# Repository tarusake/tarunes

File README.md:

# tarunes

tarunes is a NES-compatible hardware design written in Veryl. It includes a 6502-family CPU, NES-style PPU / APU, CPU and PPU buses, memory blocks, an HDMI 480p scaler, I2S audio output, and SFC controller input.

The design supports Verilator + SDL2 simulation and Tang Nano 20K hardware. It converts an iNES ROM into PRG / CHR HEX files and displays either the internal 256x240 video output or the 720x480 HDMI output.

No commercial ROM files are included in this repository.

## Project Layout

```text
tarunes/
├── Veryl.toml          # Veryl project configuration
├── Makefile            # Build, ROM conversion, and simulation targets
├── nes2hex.py          # Convert an iNES ROM into PRG / CHR HEX files
├── csv_to_opcodenotrace.py
│                       # Extract PC/opcode rows from a Gowin CSV trace
├── collapse_cpu_trace_loops.py
│                       # Collapse long wait loops in CPU traces
├── src/
│   ├── top.veryl       # Top-level module
│   ├── cpu.veryl       # CPU core
│   ├── cpu_pkg.veryl   # CPU instruction and decode definitions
│   ├── ppu.veryl       # Picture Processing Unit (PPU)
│   ├── ppu_pkg.veryl   # PPU register, OAM, and address definitions
│   ├── nes_pkg.veryl   # Shared NES address map and timing constants
│   ├── apu.veryl       # Audio Processing Unit (APU)
│   ├── i2s.veryl       # I2S transmitter
│   ├── hdmi_480p_scaler.veryl
│   │                   # Convert 256x240 video to 720x480 HDMI timing
│   ├── sfc_controller.veryl
│   │                   # SFC controller polling
│   ├── controller.veryl # $4016/$4017 controller registers
│   ├── oam_dma.veryl   # $4014 OAM DMA
│   ├── bus_cpu.veryl   # CPU bus decoder
│   ├── bus_ppu.veryl   # PPU bus decoder
│   ├── bus_if.veryl    # Bus interface
│   ├── memory.veryl    # Memory module
│   ├── tb_top.sv       # SystemVerilog testbench
│   └── tb_top.cpp      # C++ Verilator testbench driver
├── target/             # RTL generated by Veryl
├── tarunes_TangNano20k/
│                       # Tang Nano 20K wrapper, constraints, and Tcl build
├── tarunes_TangPrimer20k/
│                       # Tang Primer 20K Dock wrapper, constraints, and Tcl build
└── obj_dir/            # Verilator build output
```

## Requirements

Ubuntu 24.04 LTS or later is recommended for the simulation environment.

- [Verilator](https://www.veripool.org/verilator/) 5.0 or later
- [Veryl](https://github.com/veryl-lang/veryl) 0.22.1
- SDL2 development package (`sdl2-config`)
- SDL2_image development package (`SDL2_image.pc` visible to `pkg-config`)
- GNU Make
- GCC or Clang with C++17 support

Example for Ubuntu / Debian:

```bash
sudo apt install verilator libsdl2-dev libsdl2-image-dev make g++
```

### Installing Veryl

Veryl can be installed with `verylup`, the official Veryl toolchain installer. This project currently uses Veryl `0.22.1`.

Using Cargo:

```bash
cargo install verylup
verylup setup
verylup install 0.22.1
verylup default 0.22.1
veryl --version
```

`verylup setup` is only needed for the first installation. If `veryl --version` reports `veryl 0.22.1`, the toolchain is ready.

To update the installed toolchain:

```bash
verylup update
```

You can also install `verylup` by downloading a binary from its release page and placing it somewhere in your `PATH`. See [verylup: Veryl toolchain installer](https://veryl-lang.org/blog/verylup-veryl-toolchain-installer/) for details.

## Build

Place `<ROM name>.nes` at the repository root and run `make`.
By default, the build expects `helloworld.nes` and generates `helloworld_prg.hex` and `helloworld_chr.hex`.

```bash
make
```

To use another ROM, pass its basename through `ROM`:

```bash
make ROM=sample
```

This converts `sample.nes` into `sample_prg.hex` and `sample_chr.hex`, then passes them to Verilator through the `PROM_PATH` and `CROM_PATH` parameters.

To build with the APU disabled:

```bash
make ENABLE_APU=0
```

### Tang Nano 20K

Install Gowin EDA and make sure `gw_sh` is available in `PATH`. Then build the
bitstream with:

```bash
make tangnano20k ROM=sample
```

The bitstream is generated at
`tarunes_TangNano20k/impl/pnr/tarunes_tangnano20k.fs`. The board implementation
uses a Veryl TMDS encoder with Gowin `CLKDIV`, `OSER10`, and `TLVDS_OBUF`
primitives, so the encrypted Gowin DVI TX IP is not required.

APU audio is output through the board I2S pins. See
[`tarunes_TangNano20k/README.md`](tarunes_TangNano20k/README.md) for board pins,
clocking, and other details.

### Tang Primer 20K Dock

Tang Primer 20K uses the same Veryl TMDS encoder and has its own device and pin
constraints:

```bash
make tangprimer20k ROM=sample
```

The bitstream is generated at
`tarunes_TangPrimer20k/impl/pnr/tarunes_tangprimer20k.fs`. See
[`tarunes_TangPrimer20k/README.md`](tarunes_TangPrimer20k/README.md) for reset,
clock, audio, and Dock details.

## Simulation

Build and run the simulator:

```bash
make run
```

The simulator opens an SDL2 window and displays the internal 256x240 video output at 2x scale. A normal run also prints a CPU trace and writes `wave.fst`, which can be inspected with tools such as GTKWave.

For a faster run without the CPU trace or waveform output:

```bash
make run-fast
```

`run-fast` also uses an optimized simulator built without waveform tracing support.

Play APU audio in real time through SDL:

```bash
make run-fast ARGS="--audio"
```

Run another ROM:

```bash
make run ROM=sample
```

Generate a CPU execution trace for [Konata](https://github.com/shioyadan/Konata):

```bash
make run-fast ARGS="--konata tarunes.log --frames 1"
```

Open `tarunes.log` in Konata to inspect each instruction's internal CPU state transitions. The log also includes the PC, disassembly, instruction bytes, register values, frame number, and CPU cycle.

Stop after a fixed number of frames:

```bash
make run ARGS="--fast --frames 10"
```

Capture the HDMI 480p output instead of the internal 256x240 output:

```bash
make run-fast ARGS="--capture-hdmi --frames 10"
```

Runtime options:

- `--fast`: Disable CPU trace and waveform output
- `--audio`: Play APU audio through the SDL audio device
- `--capture-hdmi`: Display and save the 720x480 HDMI output
- `--frames N`: Stop after N completed frames
- `--dump-audio PATH`: Set the WAV output path
- `--dump-vram PATH`: Dump VRAM when the simulator exits
- `--log-ppu-writes PATH`: Log `$2006` / `$2007` writes
- `--konata PATH`: Write a Kanata v4 CPU execution trace
- `--dump-state`: Print a small PPU / WRAM state dump on exit

On exit, the simulator writes the last video frame to `last_frame.png` and audio to `apu.wav`.

Clean generated files:

```bash
make clean
```

## ROM Conversion

NES ROM files (`.nes`) can be converted into HEX files for simulation memory:

```bash
./nes2hex.py <input.nes>
```

Example:

```bash
./nes2hex.py helloworld.nes
```

Outputs:

- `helloworld_prg.hex`: PRG ROM for the CPU side
- `helloworld_chr.hex`: CHR ROM for the PPU side

For CHR RAM cartridges, no `*_chr.hex` file is generated because the ROM does not contain CHR ROM data.

## PPU

`src/ppu.veryl` provides:

- Background rendering
- Basic scroll register behavior (`v` / `t` / `w` / fine X)
- 8x8 sprite rendering through `$2003` / `$2004` OAM access
- `$4014` OAM DMA from WRAM to OAM
- VRAM / CHR ROM access control
- Palette RAM and NES palette based RGB output
- Video timing generation
- NMI / vblank / sprite zero hit

CPU-side VRAM and Palette RAM access is done through `$2006` / `$2007` style registers. Sprites are written into internal OAM through `$2003` / `$2004` style registers, then combined with background pixels in the PPU rendering path. The rendering path reads CHR ROM and VRAM, then the top-level module produces both the internal palette index and HDMI RGB output.

The current sprite implementation supports 8x8 mode, transparent pixels, sprite palettes, horizontal and vertical flipping, background priority, and sprite zero hit. `$4014` OAM DMA supports WRAM (`$0000-$1FFF`) as the transfer source, but the exact 513/514-cycle timing difference is not implemented. 8x16 sprites and sprite overflow are not implemented yet.

## CPU

`src/cpu.veryl` implements the main official 6502-family opcodes needed by the current design:

- Load / store: `LDA`, `LDX`, `LDY`, `STA`, `STX`, `STY`
- Arithmetic / logic: `ADC`, `SBC`, `CMP`, `CPX`, `CPY`, `AND`, `ORA`, `EOR`, `BIT`
- Shift / rotate / increment: `ASL`, `LSR`, `ROL`, `ROR`, `INC`, `DEC`, `INX`, `INY`, `DEX`, `DEY`
- Branch / jump / subroutine: `BCC`, `BCS`, `BNE`, `BEQ`, `BPL`, `BMI`, `BVC`, `BVS`, `JMP`, `JSR`, `RTS`, `RTI`, `BRK`
- Stack / transfer / flags: `PHA`, `PLA`, `PHP`, `PLP`, `TAX`, `TXA`, `TAY`, `TYA`, `TSX`, `TXS`, `SEI`, `SEC`, `CLI`, `CLD`, `CLC`, `SED`, `CLV`, `NOP`

Unimplemented opcodes are treated as `INVALID`. Unofficial opcodes are currently out of scope.

## APU / Audio

`src/apu.veryl` implements the basic registers and counters for two pulse channels, triangle, and noise. DMC is not implemented.

- `$4000-$4007`: pulse 1 / pulse 2
- `$4008-$400B`: triangle
- `$400C-$400F`: noise
- `$4015`: channel enable / status
- `$4017`: frame counter

The APU produces 8-bit samples. The top-level module stores them in a small FIFO, and `src/i2s.veryl` outputs them as I2S. The Verilator testbench can also save them as a WAV file.

## Video Output

`src/hdmi_480p_scaler.veryl` converts the 256x240 PPU output into a 720x480 HDMI 480p timing stream. In the Verilator testbench, `--capture-hdmi` captures frames from the HDMI-side RGB / sync / data-enable outputs.

## Memory Map

CPU side:

- `$0000-$1FFF`: WRAM
- `$2000-$2007`: PPU registers (`$2003`: OAMADDR, `$2004`: OAMDATA)
- `$4000-$4017`: APU / OAM DMA / controller registers
- `$4014`: OAM DMA, as part of `$4000-$4017`
- `$4016-$4017`: controllers
- `$8000-$FFFF`: PRG ROM

PPU side:

- `$0000-$1FFF`: CHR ROM
- `$2000-$3EFF`: VRAM
- `$3F00-$3F1F`: Palette RAM

## References

The NES-compatible behavior in this project is based mainly on the following public specification resources:

- [NESdev Wiki](https://www.nesdev.org/wiki/Nesdev_Wiki)
- [Emulator tests](https://www.nesdev.org/wiki/Emulator_tests)
- [CPU unofficial opcodes](https://www.nesdev.org/wiki/CPU_unofficial_opcodes)
- [PPU scrolling](https://www.nesdev.org/wiki/PPU_scrolling)
- [PPU palettes](https://www.nesdev.org/wiki/PPU_palettes)
- [APU](https://www.nesdev.org/wiki/APU)
- [APU Mixer](https://www.nesdev.org/wiki/APU_Mixer)
- [APU Length Counter](https://www.nesdev.org/wiki/APU_Length_Counter)
- [NES研究室 - サンプル](https://tekepen.com/nes/sample.html)

## Japanese README

Japanese documentation is available in [README_jp.md](README_jp.md).

## License

This project is released under the MIT License.

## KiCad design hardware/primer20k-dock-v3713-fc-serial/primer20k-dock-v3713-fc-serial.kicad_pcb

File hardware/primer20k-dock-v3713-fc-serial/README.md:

# Tang Primer 20K Dock V3713 - FC NROM serial cartridge reader

Tang Primer 20K Dock V3713を残したまま、実ファミコンカートリッジの
PRG ROM/CHR ROMを起動時に読み出すためのDock直挿しアダプタ基板。

## 対応範囲

- 日本版FC 60ピンカートリッジ
- Mapper 0（NROM-256、PRG ROM 32 KiB＋CHR ROM 8 KiB）
- Dock PMOD0への1コネクタ直挿し（ケーブル不要）
- PMOD1/2/3位置を一続きに切り欠き、別PMODをDockへ直接挿せる
- Dockの3.3 Vから基板上で5.0 Vを生成
- カートリッジ電源をFPGAからON/OFF
- 電源OFF時はレベル変換ICから全74HC595出力をHi-Z化し、逆給電を防止

本基板はNROMカートリッジのPRG/CHR ROMを起動時に読み出す。ダンプ後に
カートリッジ電源を切り、tarunes本体は取得済みイメージから動作する。
カートリッジバスのリアルタイムパススルーやMMC書込み回路は実装しない。

## Dock接続

DockのPMOD0へ直接挿す。HDMI、Ethernet、
USBデバッガ、オーディオ出力には干渉しない。

`ciniml/TangFPGAExtensions` の `TangPrimer_PmodExtender.kicad_pcb`を基準にする。
Dock側4コネクタは同一Yで隣接間隔19.10 mm。J2をPMOD0へ挿し、
PMOD1/2/3位置をまとめて露出する幅47.5 mm、深さ15 mmの切り欠きを設ける。
J2は秋月 `PH-2x40SG(6.1/6.1)`（販売コード112180）から2x6を1個切り出し、
基板下向きに手実装する。6.1 mmの嵌合長を確保し、JLCPCBの実装対象からは除外する。
JLCPCBで波はんだ実装まで依頼する場合の代替は
`PZ254-2-06-Z-8.5`（C2894967、嵌合長6 mm）だが、本リリースBOMでは採用しない。

PMOD3には既存のPMOD-SFCを切り欠きからDockへ直接挿せる。tarunesの既存配置は
`sfc_data=N8`、`sfc_clk=N7`、`sfc_latch=B11`で、いずれもJ5に出ている。
J5はRGB LCD端子と信号を共有するため、PMOD-SFC使用中はRGB LCDを接続しない。
HDMI出力とは競合しない。

PMOD-SFCパススルー回路は実装しない。PMOD-SFCへの電源と信号はすべて
Dock PMOD3から直接供給される。

PMOD1/2/3には本基板から電源も信号も接続しない。

| FPGA ball | Adapter signal | Direction |
|---|---|---|
| P9 | CART_SCLK | Dock -> adapter |
| T9 | CART_MOSI | Dock -> adapter |
| T8 | CART_RCLK | Dock -> adapter |
| P8 | CART_PL_N | Dock -> adapter |
| R8 | CART_MISO | adapter -> Dock |
| T6 | CART_PWR_EN | Dock -> adapter |
| P6, T7 | NC | - |

J14 pin 6/T9はDock上のWS2812にも接続されているため、ROM読み出し中にLEDが
点滅する。電気的競合はない。GowinプロジェクトではT9に
`set_option -use_sspi_as_gpio 1`が必要。

## シリアルプロトコル

秋月TC74HC595AFを5個（40 bit出力）、TC74HC165APを2個（16 bit入力）として
使用し、すべて5 Vで動作する。Dockの3.3 V制御信号はTC74VHCT540AFで
5 Vへ変換する。540は反転型なので、FPGAはMOSI/SCLK/RCLK/PLを反転して
出力する。MISOは1 kΩ/2 kΩの抵抗分圧で3.3 Vへ変換する。

出力チェーンは最初に送ったbitがU5側へ移動する。`shift-map.csv`を正本とする。

1. `CART_PWR_EN=0`で開始する。U9が595出力をHi-Zに保つ。
2. `CART_PWR_EN=1`後5 ms待つ。
3. 40 bitをMSB firstで送信し、`CART_RCLK`をLow→High→Lowにする。
4. 500 ns待ち、`CART_PL_N`をLowにして入力をラッチする。
5. `CART_PL_N=High`後、16 bitを読み出す。CPU D0-D7に続いてPPU D0-D7。
6. 全ROM読出し後`CART_PWR_EN=0`。U9が595出力をHi-Zに戻す。

PMODからU9までの4本は反転前の信号で、U9出力が実際の595/165制御信号に
なる。上記手順はカートリッジ側で観測する論理極性を示す。

初版はNROM-256固定で、PRG 32 KiBとCHR 8 KiBを読み出す。MMC1/MMC3/MMC5、
CHR RAM、NROM-128の自動判別は対象外。

シリアルクロック上限は10 MHzとする。カートリッジアクセス待ちは500 ns以上。

## 電源条件

- Dock PMOD +3V3入力: 約400 mAまでを想定し、0.8 mm配線
- FC +5V出力: 200 mA連続を設計上限
- 秋月AE-XCL102D503CR-G（販売コード113065）: 5 V、最大210 mA
- TCK107AFロードスイッチ（販売コード116072）: FPGA正論理制御
- 電源投入中のカートリッジ抜き差し禁止
- Dockへ5 Vを逆給電しない

## 製造ファイル

PCBAは使用せず、JLCPCBへは`manufacturing/gerbers.zip`だけを投入する。
部品は`manual-parts.csv`に従って秋月から購入し、すべて手実装する。

- `gerbers.zip`
- `manual-parts.csv`
- `erc.rpt`, `drc.rpt`

`bom.csv`と`cpl.csv`はPCBA非使用を明示するためヘッダーのみで、アップロード
しない。

FCコネクタJ1はユーザー支給・DNP。調達品はAliExpress item
`1005007638566482`の選択肢E「For Famicom FC 60pin」（固定耳付き）。
信号端子部はFC規格とHirose `CR22A-60D-2.54DS(70)`の公式図面を
交差チェックし、以下でフットプリントを確定する。

- 信号ピン: 2x30、2.54 mmピッチ
- 列間: 5.08 mm
- 端子列の長さ: 29 x 2.54 = 73.66 mm
- 基板穴: 1.0 mm drill、1.8 mm pad（Hirose推奨の0.8 +0.2/-0 mmを包含）

AliExpress品の固定耳は寸法図がない。商品画像を2.54 mmピッチで
画像校正した参考値は、本体幅約87 mm、全長約124 mm、固定穴中心間
約115 mm。ただし写真透視の推定なのでPCB穴には使用ず、耳は基板の外へ
オーバーハングさせる。60本のはんだ端子で固定し、耳の固定穴は本設計では
使用しない。これにより、耳の実測待ちにせずGerberを確定できる。

## 再生成

KiCad 10とpcbnew Python moduleが必要。

```bash
./build.sh
```

## 発注設定

- 2層、FR-4、1.6 mm、1 oz（両面GNDポリゴン）
- HASL lead-freeまたはENIG
- 最小配線/間隔 0.20/0.15 mm（通常配線間隔0.20 mm、U9パッド間のみ0.16 mm）
- 銅箔－基板外形クリアランス 0.30 mm
- 最大外形 約85 x 55.12 mm（PMOD1/2/3に47.5 x 10.5 mmの連続切り欠き）
- Dock直挿し保持のため、単独ケース用M3取付穴は省略
- J1は実装しない

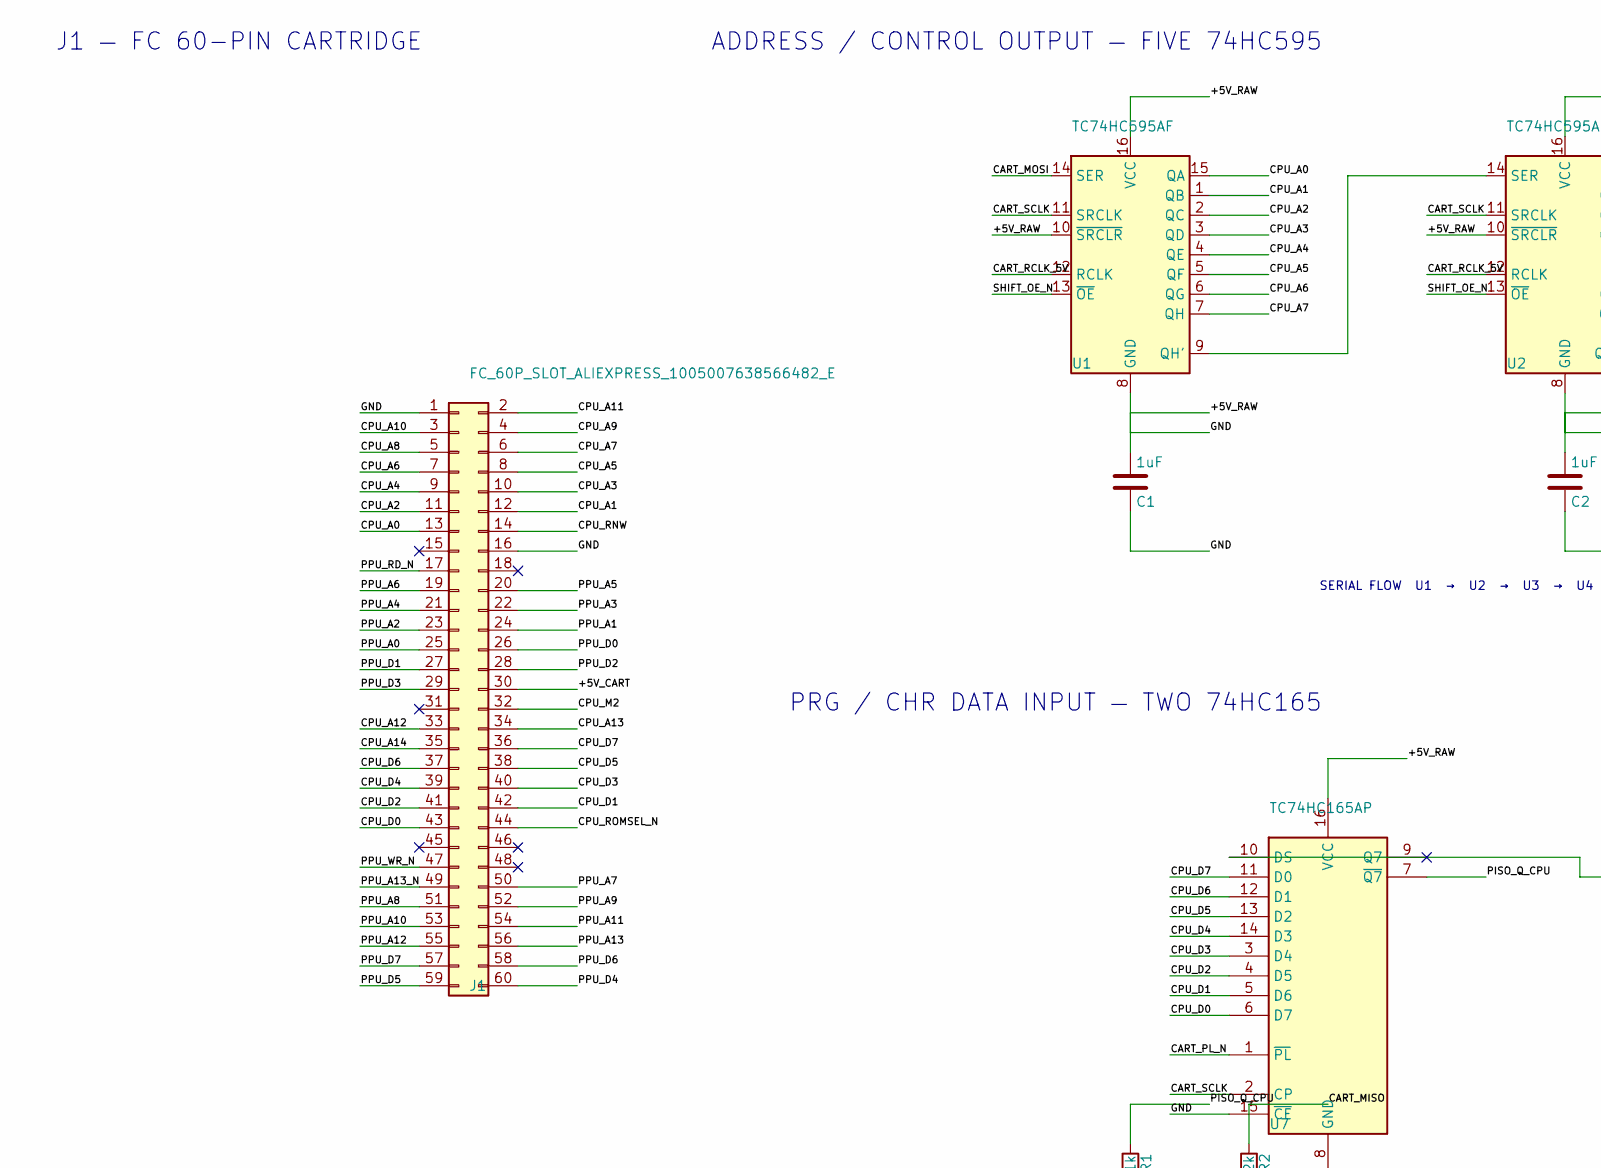
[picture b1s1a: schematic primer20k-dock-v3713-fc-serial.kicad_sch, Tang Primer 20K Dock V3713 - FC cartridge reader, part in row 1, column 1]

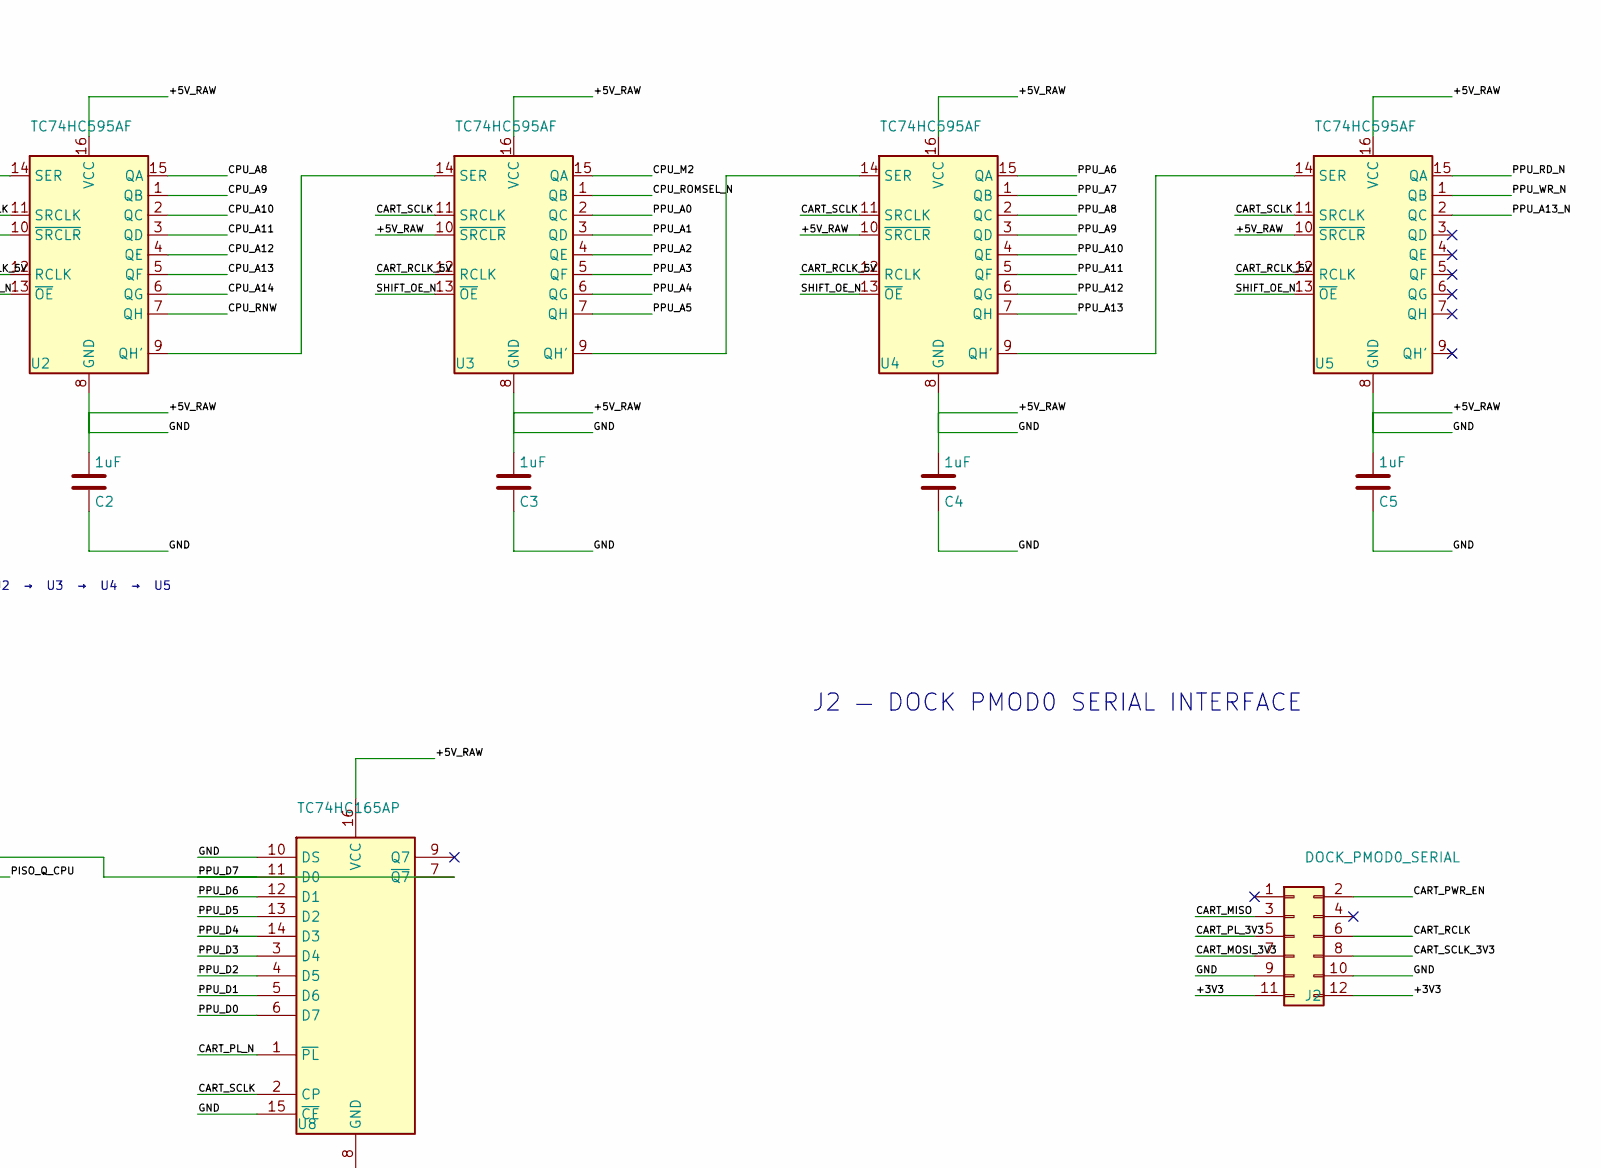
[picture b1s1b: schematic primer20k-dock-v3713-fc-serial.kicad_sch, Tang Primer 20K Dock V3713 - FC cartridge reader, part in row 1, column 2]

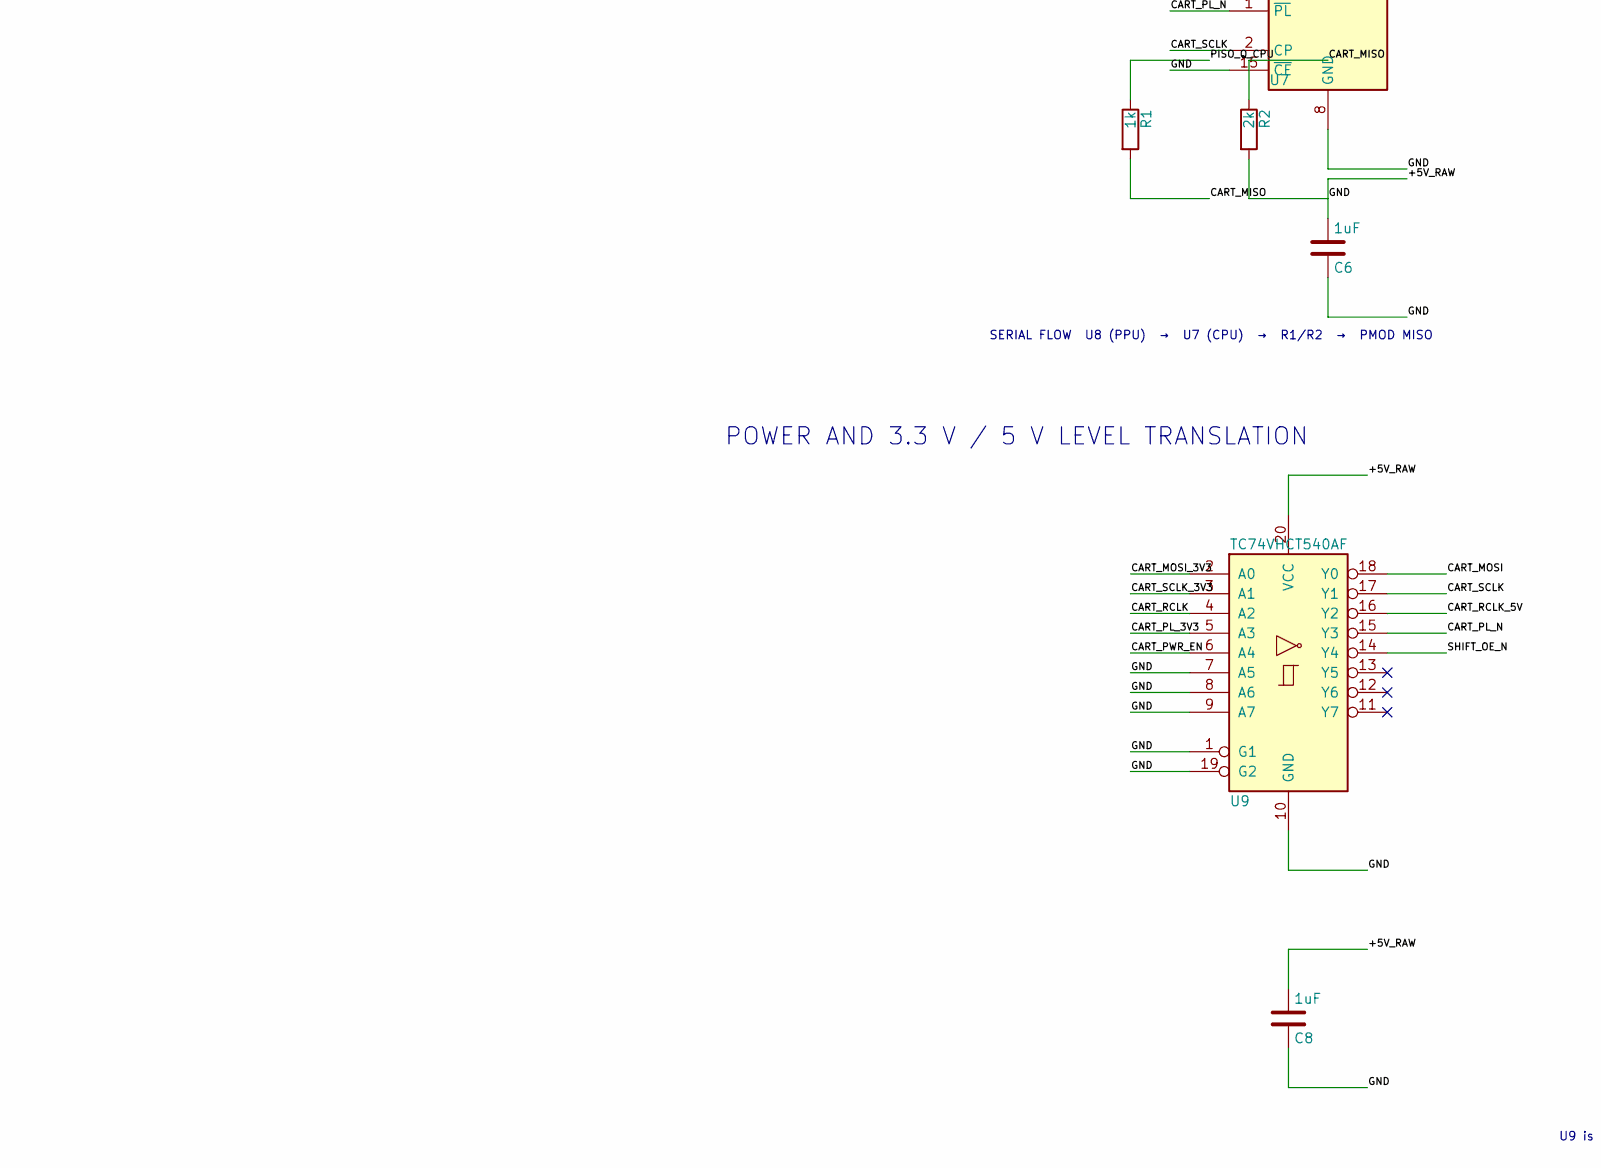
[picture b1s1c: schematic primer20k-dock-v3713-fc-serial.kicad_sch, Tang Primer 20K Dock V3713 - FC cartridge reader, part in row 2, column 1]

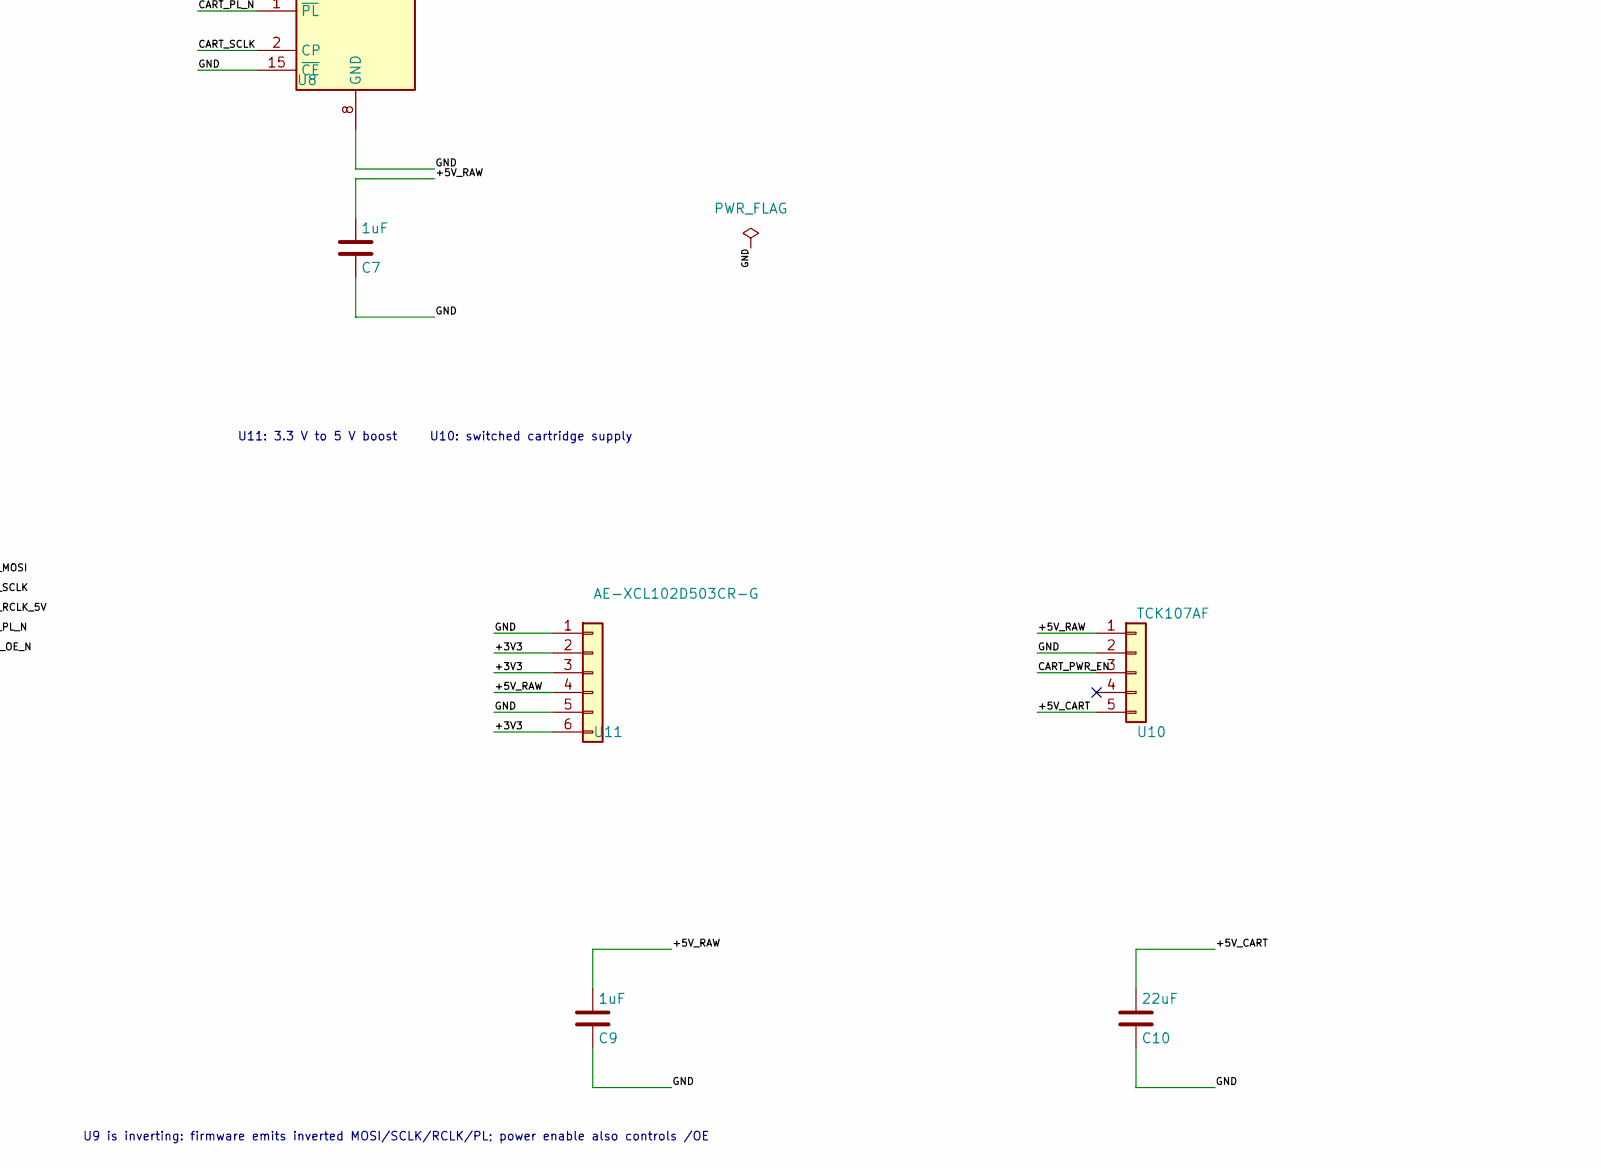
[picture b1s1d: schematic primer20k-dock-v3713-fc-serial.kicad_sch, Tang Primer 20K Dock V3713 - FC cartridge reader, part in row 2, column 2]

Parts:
C1, C2, C3, C4, C5, C6, C7, C8, C9: 1uF; C_0805_2012Metric
C10: 22uF; C_0805_2012Metric
J1: FC_60P_SLOT_ALIEXPRESS_1005007638566482_E; PinHeader_2x30_P2.54mm_Vertical
J2: DOCK_PMOD0_SERIAL; PinHeader_2x06_P2.54mm_Vertical
R1: 1k; R_Axial_DIN0207_L6.3mm_D2.5mm_P7.62mm_Horizontal
R2: 2k; R_Axial_DIN0207_L6.3mm_D2.5mm_P7.62mm_Horizontal
U1, U2, U3, U4, U5: TC74HC595AF; SOIC-16_3.9x9.9mm_P1.27mm
U7, U8: TC74HC165AP; DIP-16_W7.62mm
U9: TC74VHCT540AF; SOIC-20W_7.5x12.8mm_P1.27mm
U10: TCK107AF; SOT-23-5
U11: AE-XCL102D503CR-G; DIP-6_W7.62mm

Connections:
+3V3: J2.11, J2.12, U11.2, U11.3, U11.6
+5V_CART: C10.1, J1.30, U10.5
CART_MISO: J2.3, R1.2, R2.1
CART_MOSI: U1.14 (SER), U9.18 (Y0)
CART_MOSI_3V3: J2.7, U9.2 (A0)
CART_PL_3V3: J2.5, U9.5 (A3)
CART_PL_N: U7.1 (~PL), U8.1 (~PL), U9.15 (Y3)
CART_PWR_EN: J2.2, U9.6 (A4), U10.3
CART_RCLK: J2.6, U9.4 (A2)
CART_RCLK_5V: U1.12 (RCLK), U2.12 (RCLK), U3.12 (RCLK), U4.12 (RCLK), U5.12 (RCLK), U9.16 (Y2)
CART_SCLK: U1.11 (SRCLK), U2.11 (SRCLK), U3.11 (SRCLK), U4.11 (SRCLK), U5.11 (SRCLK), U7.2 (CP), U8.2 (CP), U9.17 (Y1)
CART_SCLK_3V3: J2.8, U9.3 (A1)
CPU_A0: J1.13, U1.15 (QA)
CPU_A1: J1.12, U1.1 (QB)
CPU_A2: J1.11, U1.2 (QC)
CPU_A3: J1.10, U1.3 (QD)
CPU_A4: J1.9, U1.4 (QE)
CPU_A5: J1.8, U1.5 (QF)
CPU_A6: J1.7, U1.6 (QG)
CPU_A7: J1.6, U1.7 (QH)
CPU_A8: J1.5, U2.15 (QA)
CPU_A9: J1.4, U2.1 (QB)
CPU_A10: J1.3, U2.2 (QC)
CPU_A11: J1.2, U2.3 (QD)
CPU_A12: J1.33, U2.4 (QE)
CPU_A13: J1.34, U2.5 (QF)
CPU_A14: J1.35, U2.6 (QG)
CPU_D0: J1.43, U7.6 (D7)
CPU_D1: J1.42, U7.5 (D6)
CPU_D2: J1.41, U7.4 (D5)
CPU_D3: J1.40, U7.3 (D4)
CPU_D4: J1.39, U7.14 (D3)
CPU_D5: J1.38, U7.13 (D2)
CPU_D6: J1.37, U7.12 (D1)
CPU_D7: J1.36, U7.11 (D0)
CPU_M2: J1.32, U3.15 (QA)
CPU_RNW: J1.14, U2.7 (QH)
CPU_ROMSEL_N: J1.44, U3.1 (QB)
LEVEL_NC6: U9.13 (Y5)
LEVEL_NC7: U9.12 (Y6)
LEVEL_NC8: U9.11 (Y7)
LOADSW_NC: U10.4
PISO_QN_7: U7.9 (Q7)
PISO_QN_8: U8.9 (Q7)
PISO_Q_CPU: R1.1, U7.7 (~Q7)
PMOD_NC1: J2.1
PMOD_NC2: J2.4
PPU_A0: J1.25, U3.2 (QC)
PPU_A1: J1.24, U3.3 (QD)
PPU_A2: J1.23, U3.4 (QE)
PPU_A3: J1.22, U3.5 (QF)
PPU_A4: J1.21, U3.6 (QG)
PPU_A5: J1.20, U3.7 (QH)
PPU_A6: J1.19, U4.15 (QA)
PPU_A7: J1.50, U4.1 (QB)
PPU_A8: J1.51, U4.2 (QC)
PPU_A9: J1.52, U4.3 (QD)
PPU_A10: J1.53, U4.4 (QE)
PPU_A11: J1.54, U4.5 (QF)
PPU_A12: J1.55, U4.6 (QG)
PPU_A13: J1.56, U4.7 (QH)
PPU_A13_N: J1.49, U5.2 (QC)
PPU_D0: J1.26, U8.6 (D7)
PPU_D1: J1.27, U8.5 (D6)
PPU_D2: J1.28, U8.4 (D5)
PPU_D3: J1.29, U8.3 (D4)
PPU_D4: J1.60, U8.14 (D3)
PPU_D5: J1.59, U8.13 (D2)
PPU_D6: J1.58, U8.12 (D1)
PPU_RD_N: J1.17, U5.15 (QA)
PPU_WR_N: J1.47, U5.1 (QB)
SHIFT_OE_N: U1.13 (~OE), U2.13 (~OE), U3.13 (~OE), U4.13 (~OE), U5.13 (~OE), U9.14 (Y4)
SHIFT_OUT_1_2: U1.9 (QH'), U2.14 (SER)
SHIFT_OUT_2_3: U2.9 (QH'), U3.14 (SER)
SHIFT_OUT_3_4: U3.9 (QH'), U4.14 (SER)
SHIFT_OUT_4_5: U4.9 (QH'), U5.14 (SER)
SHIFT_OUT_END: U5.9 (QH')
SPARE35: U5.3 (QD)
SPARE36: U5.4 (QE)
SPARE37: U5.5 (QF)
SPARE38: U5.6 (QG)
SPARE39: U5.7 (QH)

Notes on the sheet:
J1 — FC 60-PIN CARTRIDGE
ADDRESS / CONTROL OUTPUT — FIVE 74HC595
SERIAL FLOW U1 → U2 → U3 → U4 → U5
PRG / CHR DATA INPUT — TWO 74HC165
SERIAL FLOW U8 (PPU) → U7 (CPU) → R1/R2 → PMOD MISO
J2 — DOCK PMOD0 SERIAL INTERFACE
POWER AND 3.3 V / 5 V LEVEL TRANSLATION
U11: 3.3 V to 5 V boost U10: switched cartridge supply
U9 is inverting: firmware emits inverted MOSI/SCLK/RCLK/PL; power enable also controls /OE

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
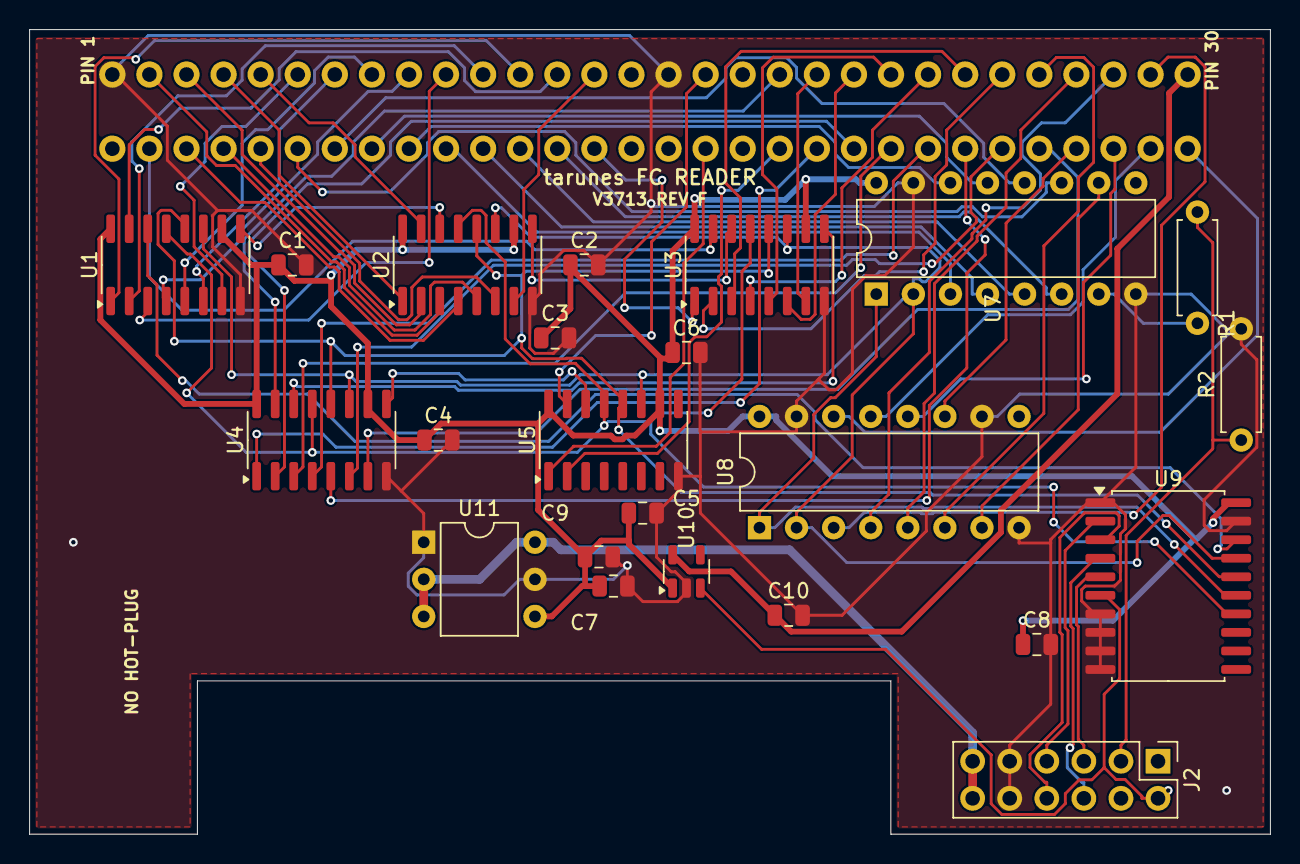
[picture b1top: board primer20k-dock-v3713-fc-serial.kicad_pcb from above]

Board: 2 copper layers, 85.0 x 55.1 mm, 24 parts (0 on the bottom side), 72 nets.

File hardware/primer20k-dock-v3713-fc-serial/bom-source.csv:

references,quantity,manufacturer,mpn,package,jlcpcb_part,assembly,notes
U1-U5,5,Toshiba,TC74HC595AF,SOP-16,110077,MANUAL_AKIZUKI,Akizuki code 110077; 5V output shift registers
U7-U8,2,Toshiba,TC74HC165AP(F),DIP-16,114679,MANUAL_AKIZUKI,Akizuki code 114679; use DIP sockets if desired
U9,1,Toshiba,TC74VHCT540AF,SOP-20,100659,MANUAL_AKIZUKI,Akizuki code 100659; inverting 3V3-to-5V control level shifter
U10,1,Toshiba,TCK107AFLF,SOT-23-5,116072,MANUAL_AKIZUKI,Akizuki code 116072; positive-logic cartridge load switch
U11,1,Akizuki,AE-XCL102D503CR-G,DIP-6,113065,MANUAL_AKIZUKI,Akizuki code 113065; 5V 210mA boost module
R1,1,Generic,CF25J1KB,Axial-7.62mm,125102,MANUAL_AKIZUKI,Akizuki code 125102; 1k MISO upper divider
R2,1,Generic,CF25J2KB,Axial-7.62mm,125202,MANUAL_AKIZUKI,Akizuki code 125202; 2k MISO lower divider
C1-C9,9,Samsung,CL21B105KPFNNNE,0805,107549,MANUAL_AKIZUKI,Akizuki code 107549; 1uF 10V X7R 2012 decoupling
C10,1,muRata,GRM21BR61E226ME44,0805,108240,MANUAL_AKIZUKI,Akizuki code 108240; 22uF 25V X5R output bulk
J2,1,Akizuki,PH-2x40SG(6.1/6.1),cut to 2x6 2.54mm,112180,MANUAL_AKIZUKI,Akizuki code 112180; cut one 2x6 section and mount below PCB for PMOD0
J1,1,ChengHaoRan,AliExpress_1005007638566482_Option_E,FC 60pin with mounting ears,,DNP,user supplied; mechanical dimensions must be measured before final Gerber
